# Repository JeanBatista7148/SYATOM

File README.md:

# SYATOM
Aqui encontraras todos los documentos del proyecto SYATOM

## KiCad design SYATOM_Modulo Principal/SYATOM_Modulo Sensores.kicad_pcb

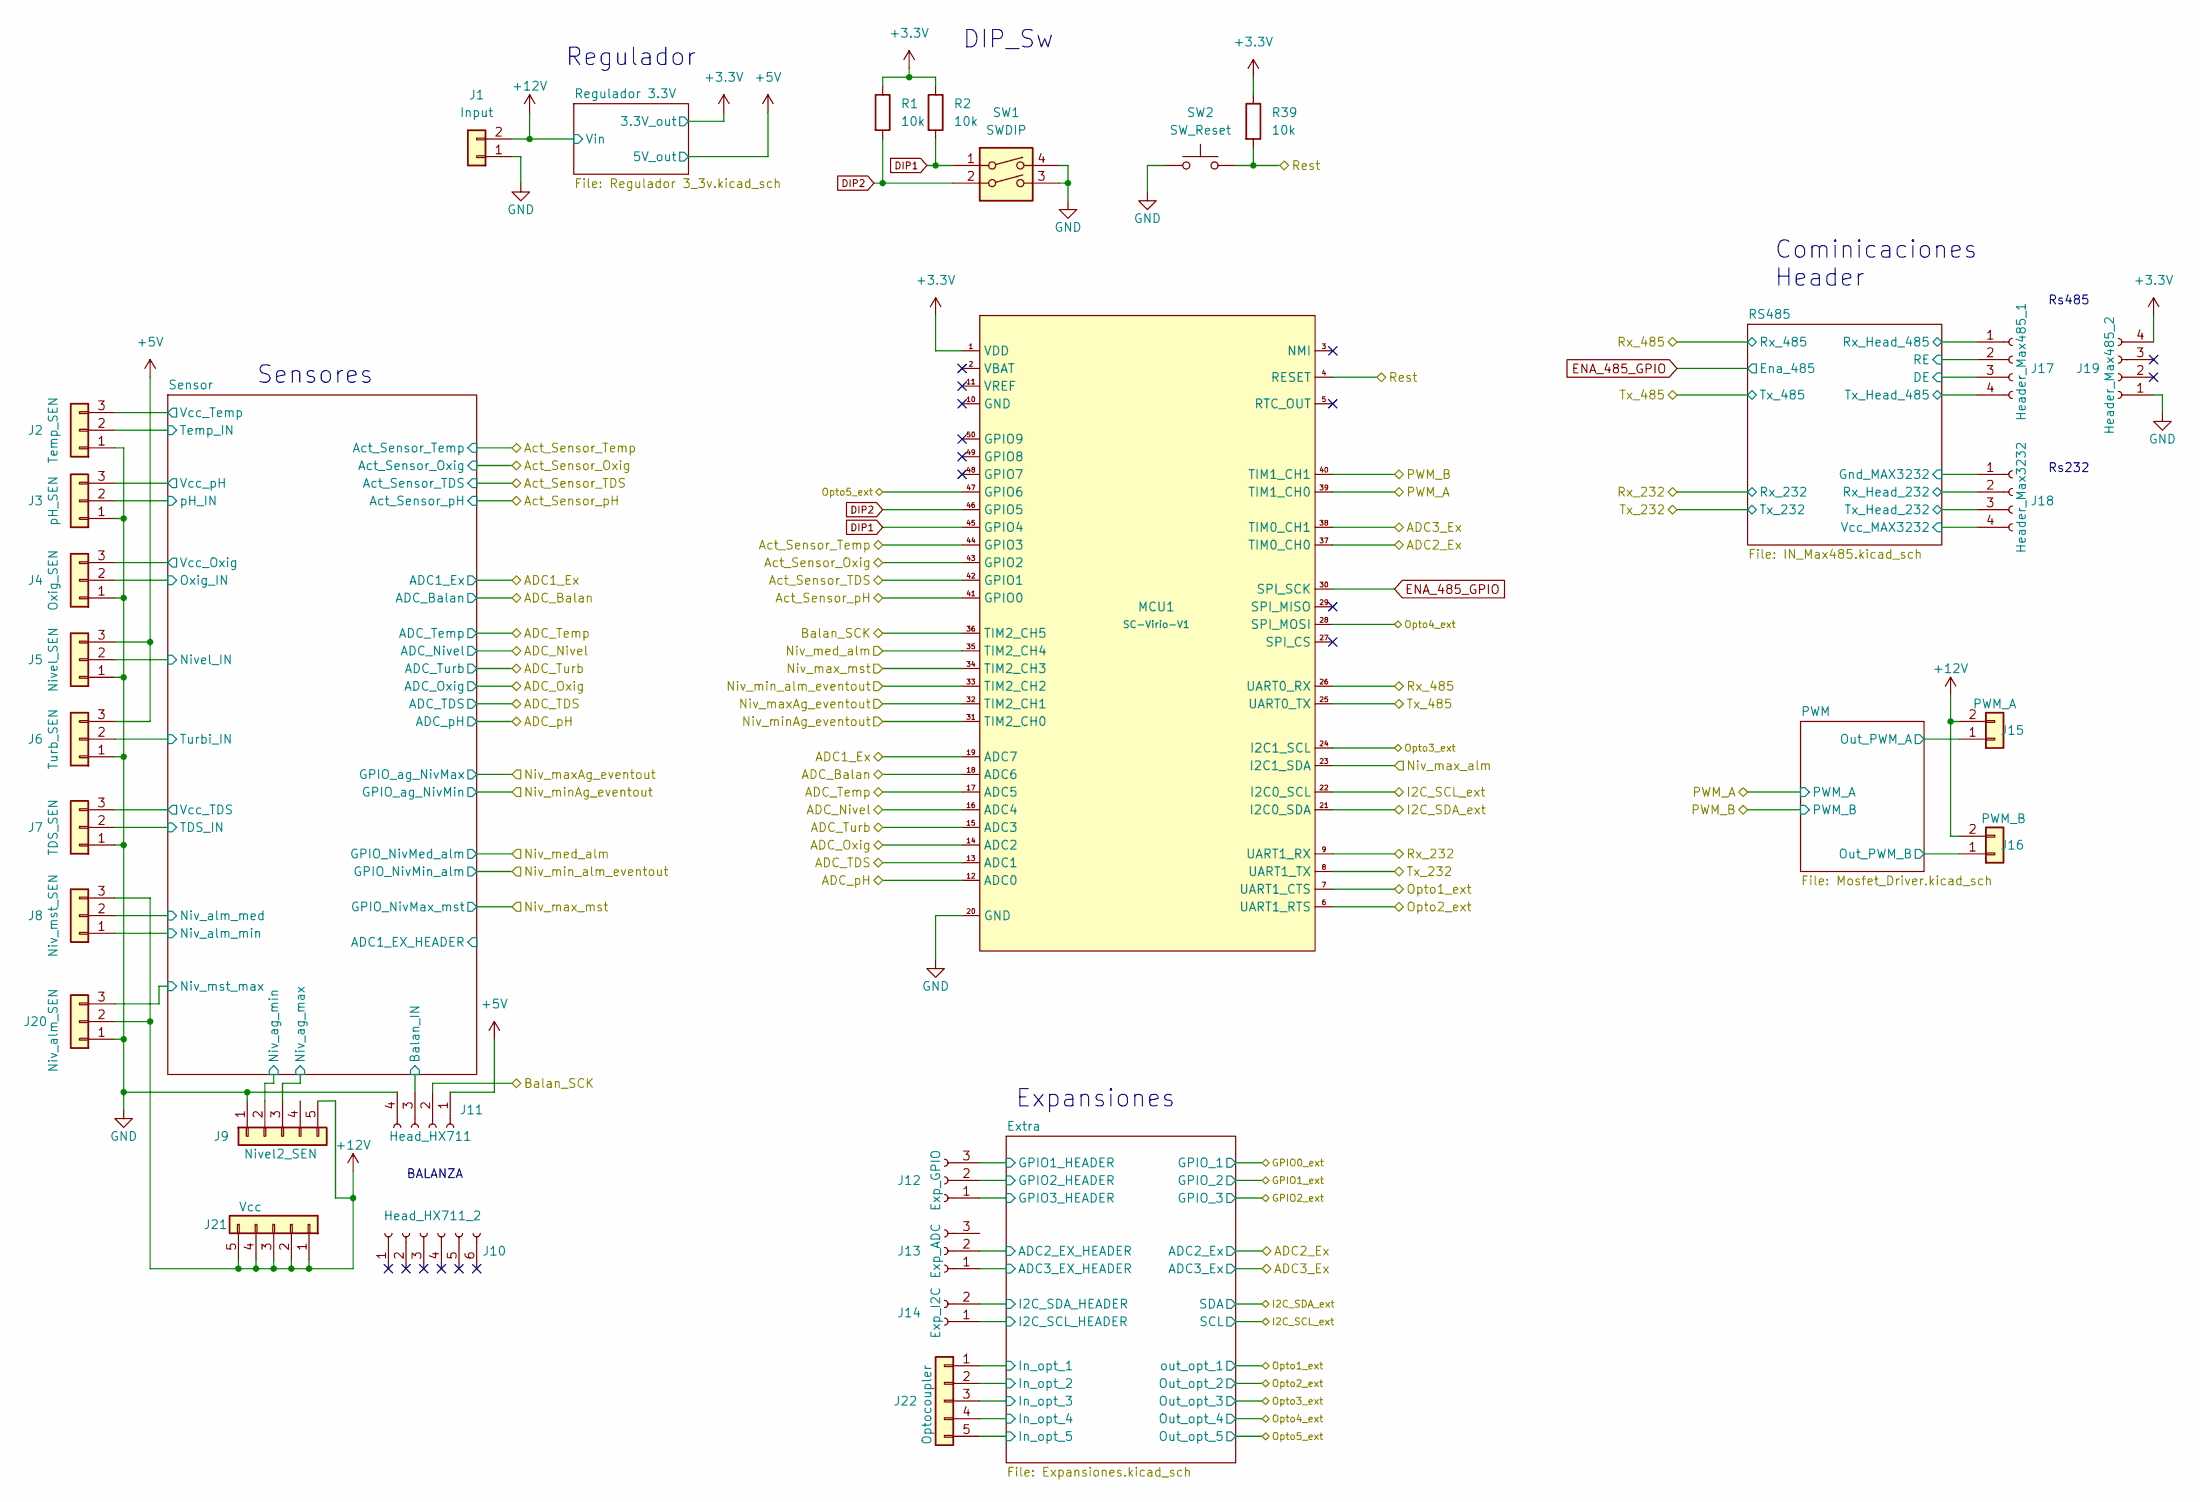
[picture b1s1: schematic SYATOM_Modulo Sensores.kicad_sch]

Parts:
J1: Input; TerminalBlock_bornier-2_P5.08mm
J2: Temp_SEN; TerminalBlock_bornier-3_P5.08mm
J3: pH_SEN; TerminalBlock_bornier-3_P5.08mm
J4: Oxig_SEN; TerminalBlock_bornier-3_P5.08mm
J5: Nivel_SEN; TerminalBlock_bornier-3_P5.08mm
J6: Turb_SEN; TerminalBlock_bornier-3_P5.08mm
J7: TDS_SEN; TerminalBlock_bornier-3_P5.08mm
J8: Niv_mst_SEN; TerminalBlock_bornier-3_P5.08mm
J9: Nivel2_SEN; TerminalBlock_bornier-5_P5.08mm
J10: Head_HX711_2; PinSocket_1x06_P2.54mm_Vertical
J11: Head_HX711; PinSocket_1x04_P2.54mm_Vertical
J12: Exp_GPIO; PinSocket_1x03_P2.54mm_Vertical
J13: Exp_ADC; PinSocket_1x03_P2.54mm_Vertical
J14: Exp_I2C; PinSocket_1x02_P2.54mm_Vertical
J15: PWM_A; TerminalBlock_bornier-2_P5.08mm
J16: PWM_B; TerminalBlock_bornier-2_P5.08mm
J17: Header_Max485_1; PinSocket_1x04_P2.54mm_Vertical
J18: Header_Max3232; PinSocket_1x04_P2.54mm_Vertical
J19: Header_Max485_2; PinSocket_1x04_P2.54mm_Vertical
J20: Niv_alm_SEN; TerminalBlock_bornier-3_P5.08mm
J21: Vcc; TerminalBlock_bornier-5_P5.08mm
J22: Optocoupler; TerminalBlock_bornier-5_P5.08mm
MCU1: SC-Virio-V1; SC-VIRIO-V1
R1, R2, R39: 10k; R_0603_1608Metric
SW1: SWDIP; SW_DIP_SPSTx02_Slide_9.78x7.26mm_W7.62mm_P2.54mm
SW2: SW_Reset; SW_SPST_B3S-1000

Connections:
+3V3: J18.4, J19.4, MCU1.1 (VDD), R1.1, R2.1, R39.1; also elsewhere on the board
+5V: J5.3, J6.3, J11.1; also elsewhere on the board
+12V: J1.2, J8.3, J9.5, J15.2, J16.2, J20.2, J21.1, J21.2, J21.3, J21.4, J21.5; also elsewhere on the board
/ADC1_Ex: MCU1.19 (ADC7); also elsewhere on the board
/ADC2_Ex: MCU1.37 (TIM0_CH0); also elsewhere on the board
/ADC3_Ex: MCU1.38 (TIM0_CH1); also elsewhere on the board
/ADC_Balan: MCU1.18 (ADC6); also elsewhere on the board
/ADC_Nivel: MCU1.16 (ADC4); also elsewhere on the board
/ADC_Oxig: MCU1.14 (ADC2); also elsewhere on the board
/ADC_TDS: MCU1.13 (ADC1); also elsewhere on the board
/ADC_Temp: MCU1.17 (ADC5); also elsewhere on the board
/ADC_Turb: MCU1.15 (ADC3); also elsewhere on the board
/ADC_pH: MCU1.12 (ADC0); also elsewhere on the board
/Act_Sensor_Oxig: MCU1.43 (GPIO2); also elsewhere on the board
/Act_Sensor_TDS: MCU1.42 (GPIO1); also elsewhere on the board
/Act_Sensor_Temp: MCU1.44 (GPIO3); also elsewhere on the board
/Act_Sensor_pH: MCU1.41 (GPIO0); also elsewhere on the board
/Balan_SCK: J11.2, MCU1.36 (TIM2_CH5)
/Extra/ADC2_EX_HEADER: J13.2; also elsewhere on the board
/Extra/ADC3_EX_HEADER: J13.1; also elsewhere on the board
/Extra/In_opt_1: J22.1; also elsewhere on the board
/Extra/In_opt_2: J22.2; also elsewhere on the board
/Extra/In_opt_3: J22.3; also elsewhere on the board
/Extra/In_opt_4: J22.4; also elsewhere on the board
/Extra/In_opt_5: J22.5; also elsewhere on the board
/GPIO0_ext: J12.3; also elsewhere on the board
/GPIO1_ext: J12.2; also elsewhere on the board
/GPIO2_ext: J12.1; also elsewhere on the board
/I2C_SCL_ext: J14.1, MCU1.22 (I2C0_SCL); also elsewhere on the board
/I2C_SDA_ext: J14.2, MCU1.21 (I2C0_SDA); also elsewhere on the board
/Niv_maxAg_eventout: MCU1.32 (TIM2_CH1); also elsewhere on the board
/Niv_max_alm: MCU1.23 (I2C1_SDA)
/Niv_max_mst: MCU1.34 (TIM2_CH3); also elsewhere on the board
/Niv_med_alm: MCU1.35 (TIM2_CH4); also elsewhere on the board
/Niv_minAg_eventout: MCU1.31 (TIM2_CH0); also elsewhere on the board
/Niv_min_alm_eventout: MCU1.33 (TIM2_CH2); also elsewhere on the board
/Opto1_ext: MCU1.7 (UART1_CTS); also elsewhere on the board
/Opto2_ext: MCU1.6 (UART1_RTS); also elsewhere on the board
/Opto3_ext: MCU1.24 (I2C1_SCL); also elsewhere on the board
/Opto4_ext: MCU1.28 (SPI_MOSI); also elsewhere on the board
/Opto5_ext: MCU1.47 (GPIO6); also elsewhere on the board
/PWM/Out_PWM_A: J15.1; also elsewhere on the board
/PWM/Out_PWM_B: J16.1; also elsewhere on the board
/PWM_A: MCU1.39 (TIM1_CH0); also elsewhere on the board
/PWM_B: MCU1.40 (TIM1_CH1); also elsewhere on the board
/Rest: MCU1.4 (RESET), R39.2, SW2.2
/Rx_232: J18.2, MCU1.9 (UART1_RX); also elsewhere on the board
/Rx_485: J17.1, MCU1.26 (UART0_RX); also elsewhere on the board
/Sensor /Balan_IN: J11.3; also elsewhere on the board
/Sensor /Niv_ag_max: J9.3; also elsewhere on the board
/Sensor /Niv_ag_min: J9.2; also elsewhere on the board
/Sensor /Niv_alm_med: J8.2; also elsewhere on the board
/Sensor /Niv_alm_min: J8.1; also elsewhere on the board
/Sensor /Niv_mst_max: J20.3; also elsewhere on the board
/Sensor /Nivel_IN: J5.2; also elsewhere on the board
/Sensor /Oxig_IN: J4.2; also elsewhere on the board
/Sensor /TDS_IN: J7.2; also elsewhere on the board
/Sensor /Temp_IN: J2.2; also elsewhere on the board
/Sensor /Turbi_IN: J6.2; also elsewhere on the board
/Sensor /Vcc_Oxig: J4.3; also elsewhere on the board
/Sensor /Vcc_TDS: J7.3; also elsewhere on the board
/Sensor /Vcc_Temp: J2.3; also elsewhere on the board
/Sensor /Vcc_pH: J3.3; also elsewhere on the board
/Sensor /pH_IN: J3.2; also elsewhere on the board
/Tx_232: J18.3, MCU1.8 (UART1_TX); also elsewhere on the board
/Tx_485: J17.4, MCU1.25 (UART0_TX); also elsewhere on the board
DIP1: MCU1.45 (GPIO4), R2.2, SW1.1
DIP2: MCU1.46 (GPIO5), R1.2, SW1.2
ENA_485_GPIO: J17.2, J17.3, MCU1.30 (SPI_SCK); also elsewhere on the board
GND: J1.1, J2.1, J3.1, J4.1, J5.1, J6.1, J7.1, J9.1, J11.4, J18.1, J19.1, J20.1, MCU1.20 (GND), SW1.3, SW1.4, SW2.1; also elsewhere on the board

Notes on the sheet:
Cominicaciones Header
Rs485
Regulador
Rs232
Sensores
DIP_Sw
Expansiones
BALANZA

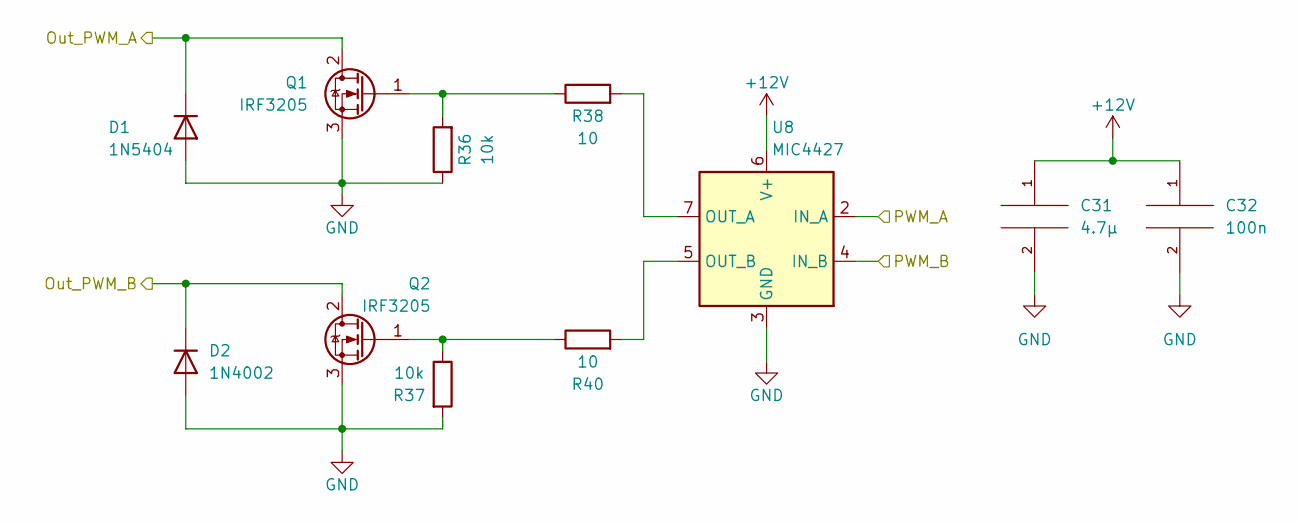
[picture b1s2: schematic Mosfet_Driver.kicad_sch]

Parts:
C31: 4.7µ; C_0805_2012Metric
C32: 100n; C_0603_1608Metric
D1: 1N5404; D_DO-201AD_P15.24mm_Horizontal
D2: 1N4002; D_DO-41_SOD81_P10.16mm_Horizontal
Q1, Q2: IRF3205; TO-220-3_Vertical
R36, R37: 10k; R_0603_1608Metric
R38, R40: 10; R_0603_1608Metric
U8: MIC4427; SOIC-8_3.9x4.9mm_P1.27mm

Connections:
+12V: C31.1, C32.1, U8.6 (V+); also elsewhere on the board
/PWM/Out_PWM_A: D1.1 (K), Q1.2 (D); also elsewhere on the board
/PWM/Out_PWM_B: D2.1 (K), Q2.2 (D); also elsewhere on the board
/PWM_A: U8.2 (IN_A); also elsewhere on the board
/PWM_B: U8.4 (IN_B); also elsewhere on the board
GND: C31.2, C32.2, D1.2 (A), D2.2 (A), Q1.3 (S), Q2.3 (S), R36.1, R37.2, U8.3 (GND); also elsewhere on the board
unnamed: Q1.1 (G), R36.2, R38.1
unnamed: Q2.1 (G), R37.1, R40.1
unnamed: R38.2, U8.7 (OUT_A)
unnamed: R40.2, U8.5 (OUT_B)

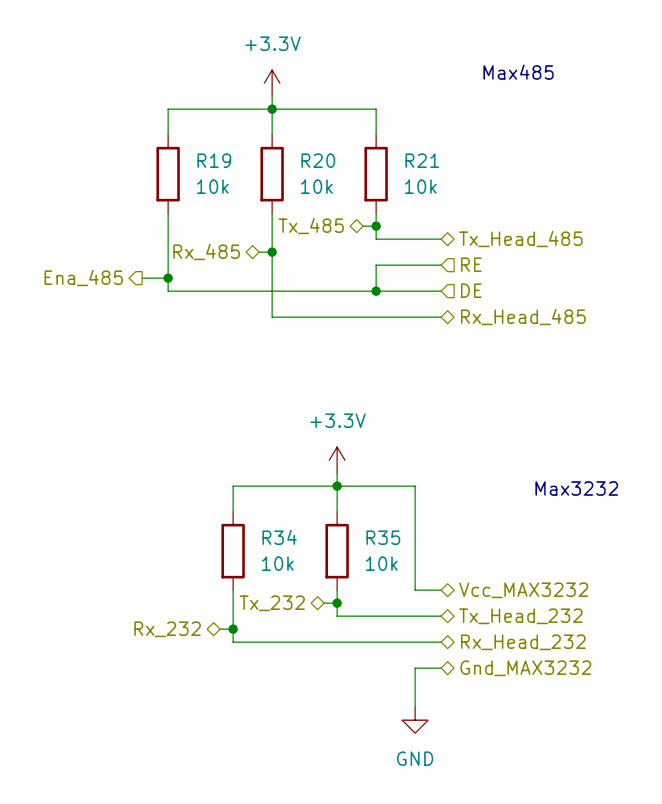
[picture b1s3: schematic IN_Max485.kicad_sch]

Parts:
R19, R20, R21, R34, R35: 10k; R_0603_1608Metric

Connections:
+3V3: R19.1, R20.1, R21.1, R34.1, R35.1; also elsewhere on the board
/Rx_232: R34.2; also elsewhere on the board
/Rx_485: R20.2; also elsewhere on the board
/Tx_232: R35.2; also elsewhere on the board
/Tx_485: R21.2; also elsewhere on the board
ENA_485_GPIO: R19.2; also elsewhere on the board

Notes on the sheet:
Max3232
Max485

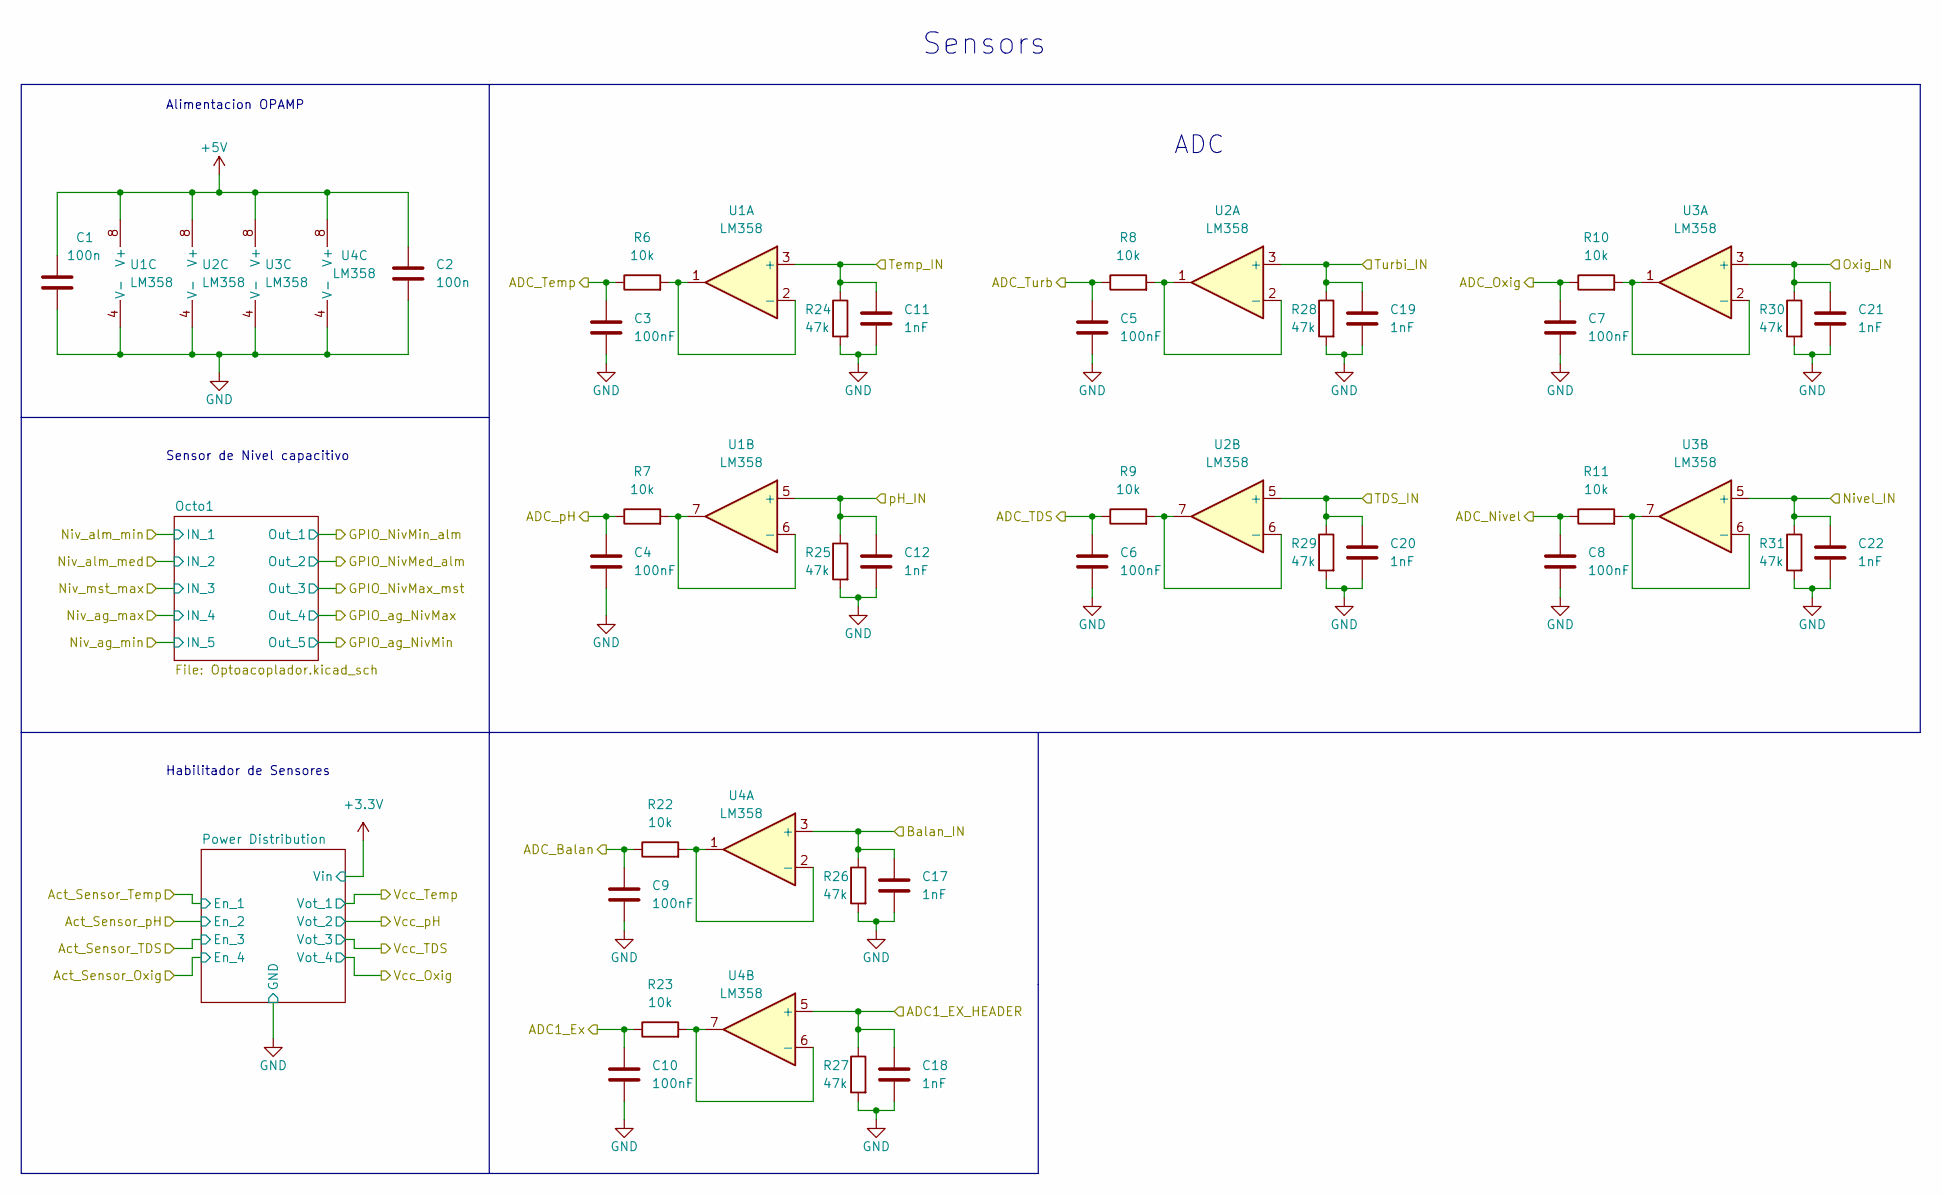
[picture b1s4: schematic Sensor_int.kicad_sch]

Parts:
C1, C2: 100n; C_0603_1608Metric
C3, C4, C5, C6, C7, C8, C9, C10: 100nF; C_0603_1608Metric
C11, C12, C17, C18, C19, C20, C21, C22: 1nF; C_0603_1608Metric
R6, R7, R8, R9, R10, R11, R22, R23: 10k; R_0603_1608Metric
R24, R25, R26, R27, R28, R29, R30, R31: 47k; R_0603_1608Metric
U1, U2, U3, U4: LM358; SOIC-8_3.9x4.9mm_P1.27mm

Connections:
+5V: C1.1, C2.1, U1.8 (V+), U2.8 (V+), U3.8 (V+), U4.8 (V+); also elsewhere on the board
/ADC1_Ex: C10.1, R23.1; also elsewhere on the board
/ADC_Balan: C9.1, R22.1; also elsewhere on the board
/ADC_Nivel: C8.1, R11.1; also elsewhere on the board
/ADC_Oxig: C7.1, R10.1; also elsewhere on the board
/ADC_TDS: C6.1, R9.1; also elsewhere on the board
/ADC_Temp: C3.1, R6.1; also elsewhere on the board
/ADC_Turb: C5.1, R8.1; also elsewhere on the board
/ADC_pH: C4.1, R7.1; also elsewhere on the board
/Sensor /ADC1_EX_HEADER: C18.1, R27.1, U4.5 (+)
/Sensor /Balan_IN: C17.1, R26.1, U4.3 (+); also elsewhere on the board
/Sensor /Nivel_IN: C22.1, R31.1, U3.5 (+); also elsewhere on the board
/Sensor /Oxig_IN: C21.1, R30.1, U3.3 (+); also elsewhere on the board
/Sensor /TDS_IN: C20.1, R29.1, U2.5 (+); also elsewhere on the board
/Sensor /Temp_IN: C11.1, R24.1, U1.3 (+); also elsewhere on the board
/Sensor /Turbi_IN: C19.1, R28.1, U2.3 (+); also elsewhere on the board
/Sensor /pH_IN: C12.1, R25.1, U1.5 (+); also elsewhere on the board
GND: C1.2, C2.2, C3.2, C4.2, C5.2, C6.2, C7.2, C8.2, C9.2, C10.2, C11.2, C12.2, C17.2, C18.2, C19.2, C20.2, C21.2, C22.2, R24.2, R25.2, R26.2, R27.2, R28.2, R29.2, R30.2, R31.2, U1.4 (V-), U2.4 (V-), U3.4 (V-), U4.4 (V-); also elsewhere on the board
unnamed: R6.2, U1.1, U1.2 (-)
unnamed: R7.2, U1.6 (-), U1.7
unnamed: R8.2, U2.1, U2.2 (-)
unnamed: R9.2, U2.6 (-), U2.7
unnamed: R10.2, U3.1, U3.2 (-)
unnamed: R11.2, U3.6 (-), U3.7
unnamed: R22.2, U4.1, U4.2 (-)
unnamed: R23.2, U4.6 (-), U4.7

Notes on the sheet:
ADC
Sensor de Nivel capacitivo
Sensors
Habilitador de Sensores
Alimentacion OPAMP

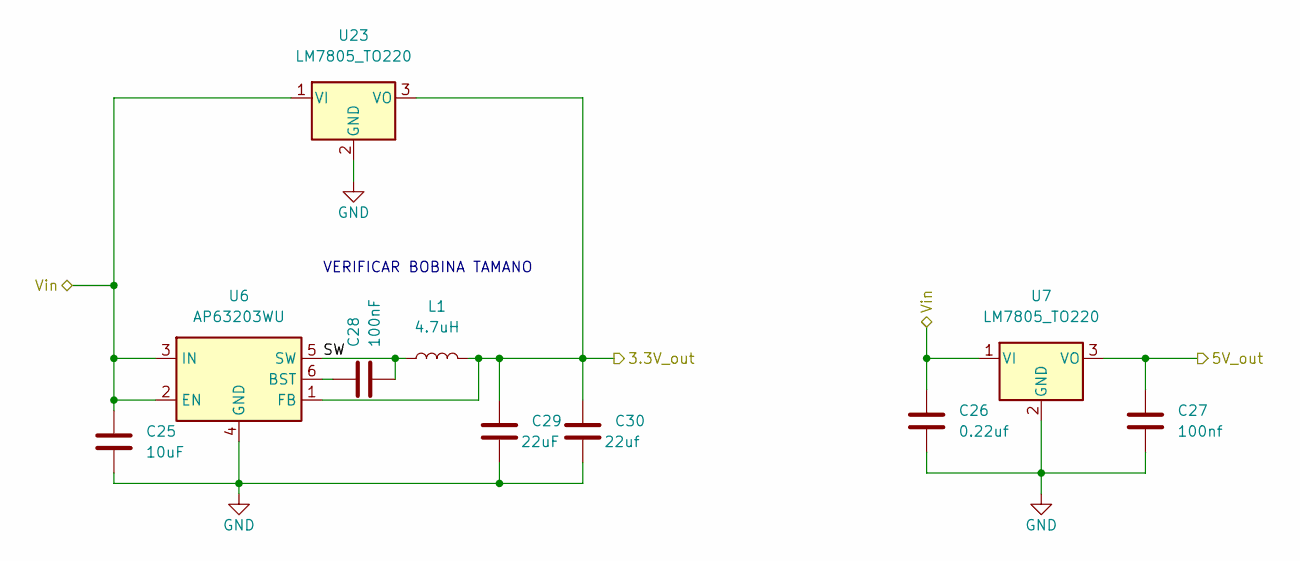
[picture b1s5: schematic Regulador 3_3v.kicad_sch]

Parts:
C25: 10uF; C_0805_2012Metric
C26: 0.22uf; C_0805_2012Metric
C27: 100nf; C_0603_1608Metric
C28: 100nF; C_0603_1608Metric
C29: 22uF; C_0805_2012Metric
C30: 22uf; C_0805_2012Metric
L1: 4.7uH; L_Bourns_SRN6045TA
U6: AP63203WU; TSOT-23-6
U7, U23: LM7805_TO220; TO-220-3_Vertical

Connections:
+3V3: C29.1, C30.1, L1.2, U6.1 (FB), U23.3 (VO); also elsewhere on the board
+5V: C27.1, U7.3 (VO); also elsewhere on the board
+12V: C25.1, C26.1, U6.2 (EN), U6.3 (IN), U7.1 (VI), U23.1 (VI); also elsewhere on the board
GND: C25.2, C26.2, C27.2, C29.2, C30.2, U6.4 (GND), U7.2 (GND), U23.2 (GND); also elsewhere on the board
unnamed: C28.1, L1.1, U6.5 (SW)
unnamed: C28.2, U6.6 (BST)

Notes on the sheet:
VERIFICAR BOBINA TAMANO

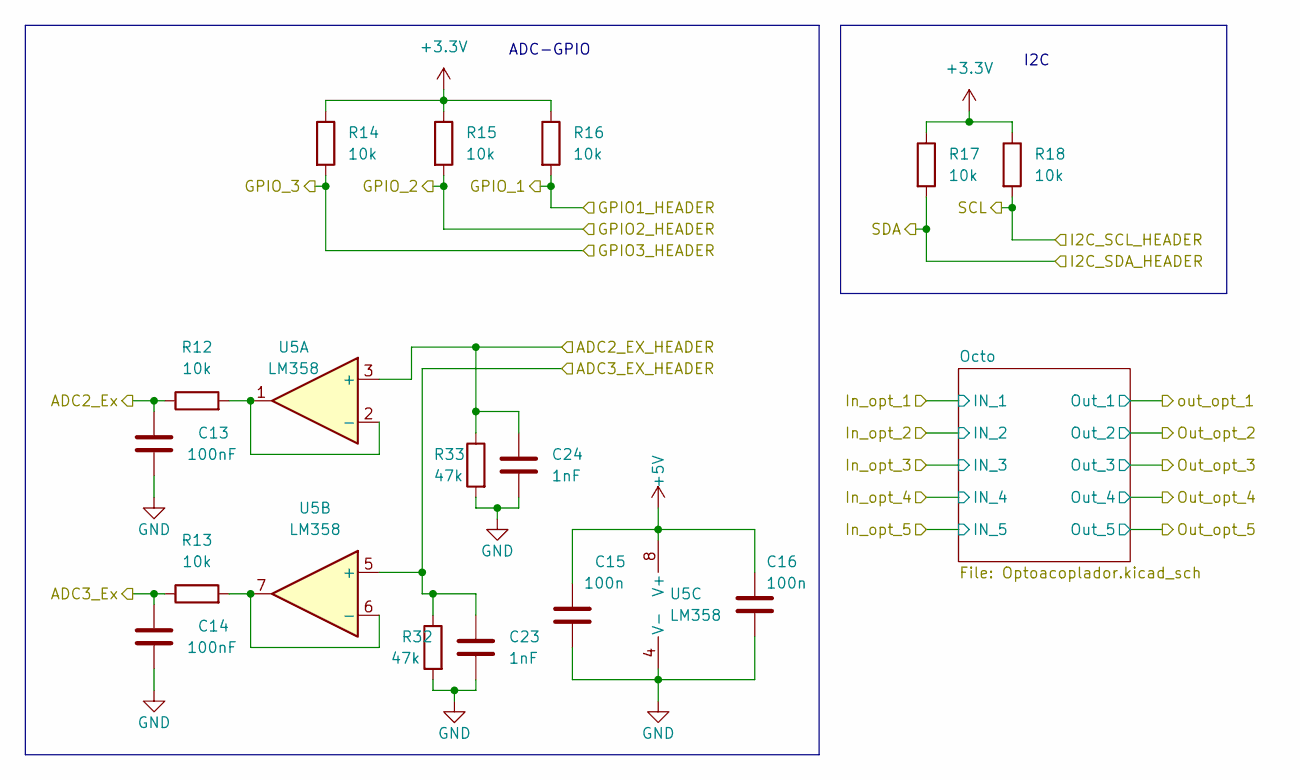
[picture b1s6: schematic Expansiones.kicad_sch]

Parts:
C13, C14: 100nF; C_0603_1608Metric
C15, C16: 100n; C_0603_1608Metric
C23, C24: 1nF; C_0603_1608Metric
R12, R13, R14, R15, R16, R17, R18: 10k; R_0603_1608Metric
R32, R33: 47k; R_0603_1608Metric
U5: LM358; SOIC-8_3.9x4.9mm_P1.27mm

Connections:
+3V3: R14.1, R15.1, R16.1, R17.1, R18.1; also elsewhere on the board
+5V: C15.1, C16.1, U5.8 (V+); also elsewhere on the board
/ADC2_Ex: C13.1, R12.1; also elsewhere on the board
/ADC3_Ex: C14.1, R13.1; also elsewhere on the board
/Extra/ADC2_EX_HEADER: C24.1, R33.1, U5.3 (+); also elsewhere on the board
/Extra/ADC3_EX_HEADER: C23.1, R32.1, U5.5 (+); also elsewhere on the board
/GPIO0_ext: R16.2; also elsewhere on the board
/GPIO1_ext: R15.2; also elsewhere on the board
/GPIO2_ext: R14.2; also elsewhere on the board
/I2C_SCL_ext: R18.2; also elsewhere on the board
/I2C_SDA_ext: R17.2; also elsewhere on the board
GND: C13.2, C14.2, C15.2, C16.2, C23.2, C24.2, R32.2, R33.2, U5.4 (V-); also elsewhere on the board
unnamed: R12.2, U5.1, U5.2 (-)
unnamed: R13.2, U5.6 (-), U5.7

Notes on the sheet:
ADC-GPIO
I2C

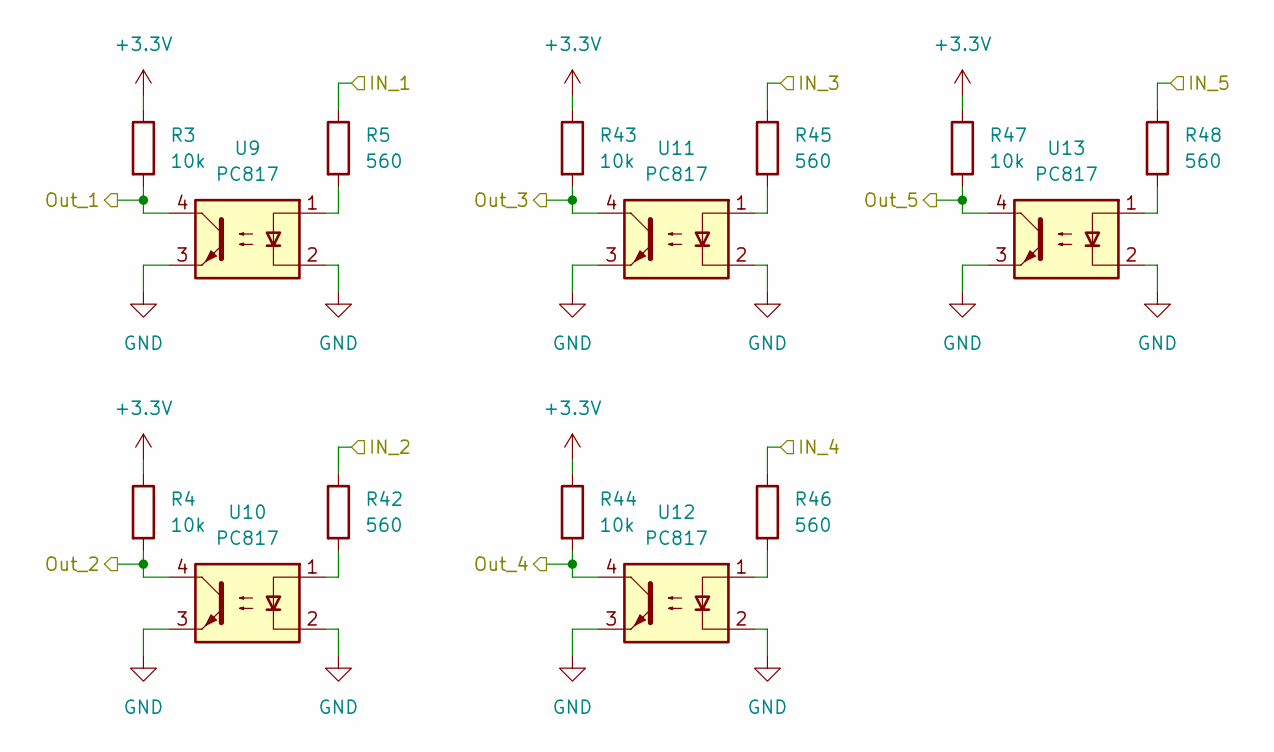
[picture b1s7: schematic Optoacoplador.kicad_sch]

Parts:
R3, R4, R43, R44, R47: 10k; R_0603_1608Metric
R5, R42, R45, R46, R48: 560; R_0603_1608Metric
U9, U10, U11, U12, U13: PC817; DIP-4_W7.62mm_SMDSocket_SmallPads

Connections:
+3V3: R3.1, R4.1, R43.1, R44.1, R47.1; also elsewhere on the board
/Niv_maxAg_eventout: R44.2, U12.4; also elsewhere on the board
/Niv_max_mst: R43.2, U11.4; also elsewhere on the board
/Niv_med_alm: R4.2, U10.4; also elsewhere on the board
/Niv_minAg_eventout: R47.2, U13.4; also elsewhere on the board
/Niv_min_alm_eventout: R3.2, U9.4; also elsewhere on the board
/Sensor /Niv_ag_max: R46.1; also elsewhere on the board
/Sensor /Niv_ag_min: R48.1; also elsewhere on the board
/Sensor /Niv_alm_med: R42.1; also elsewhere on the board
/Sensor /Niv_alm_min: R5.1; also elsewhere on the board
/Sensor /Niv_mst_max: R45.1; also elsewhere on the board
GND: U9.2, U9.3, U10.2, U10.3, U11.2, U11.3, U12.2, U12.3, U13.2, U13.3; also elsewhere on the board
unnamed: R5.2, U9.1
unnamed: R42.2, U10.1
unnamed: R45.2, U11.1
unnamed: R46.2, U12.1
unnamed: R48.2, U13.1

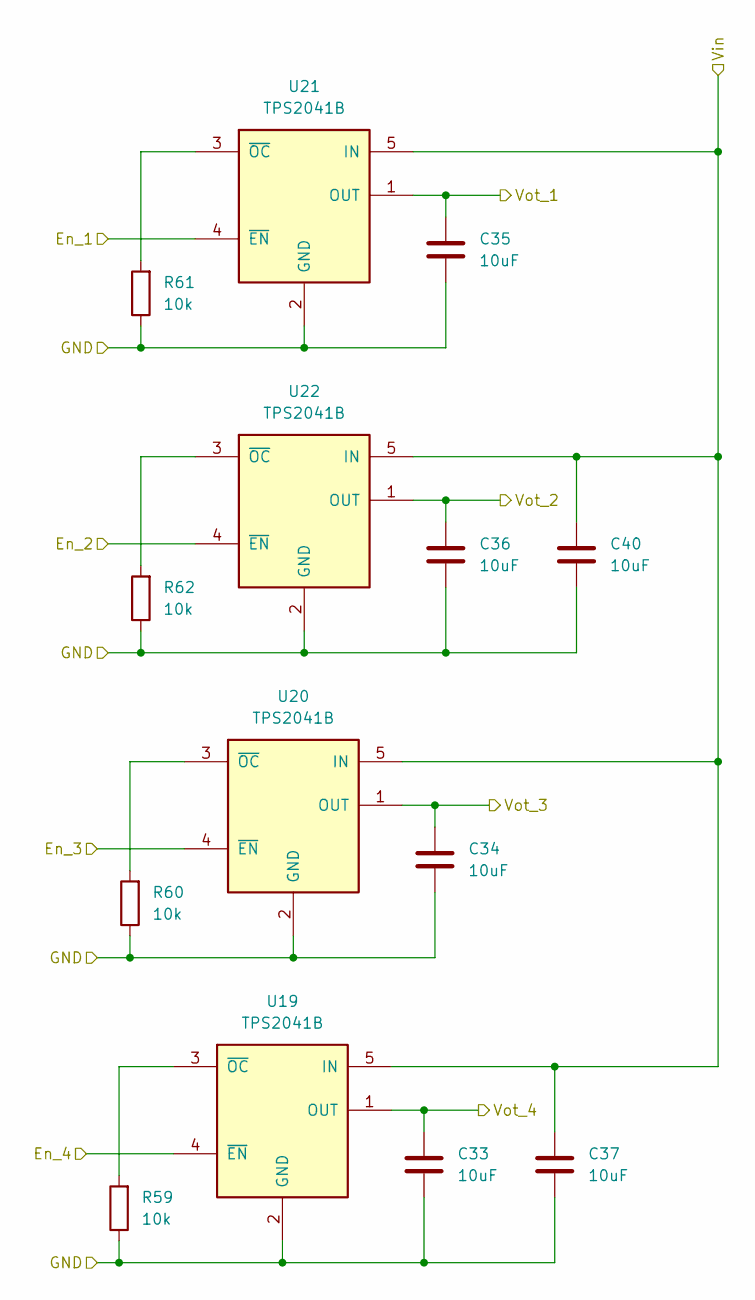
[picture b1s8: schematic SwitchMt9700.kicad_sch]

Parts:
C33, C34, C35, C36, C37, C40: 10uF; C_0805_2012Metric
R59, R60, R61, R62: 10k; R_0603_1608Metric
U19, U20, U21, U22: TPS2041B; SOT-23-5

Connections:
+3V3: C37.1, C40.1, U19.5 (IN), U20.5 (IN), U21.5 (IN), U22.5 (IN); also elsewhere on the board
/Act_Sensor_Oxig: U19.4 (~EN); also elsewhere on the board
/Act_Sensor_TDS: U20.4 (~EN); also elsewhere on the board
/Act_Sensor_Temp: U21.4 (~EN); also elsewhere on the board
/Act_Sensor_pH: U22.4 (~EN); also elsewhere on the board
/Sensor /Vcc_Oxig: C33.1, U19.1 (OUT); also elsewhere on the board
/Sensor /Vcc_TDS: C34.1, U20.1 (OUT); also elsewhere on the board
/Sensor /Vcc_Temp: C35.1, U21.1 (OUT); also elsewhere on the board
/Sensor /Vcc_pH: C36.1, U22.1 (OUT); also elsewhere on the board
GND: C33.2, C34.2, C35.2, C36.2, C37.2, C40.2, R59.1, R60.1, R61.1, R62.1, U19.2 (GND), U20.2 (GND), U21.2 (GND), U22.2 (GND); also elsewhere on the board
unnamed: R59.2, U19.3 (~OC)
unnamed: R60.2, U20.3 (~OC)
unnamed: R61.2, U21.3 (~OC)
unnamed: R62.2, U22.3 (~OC)

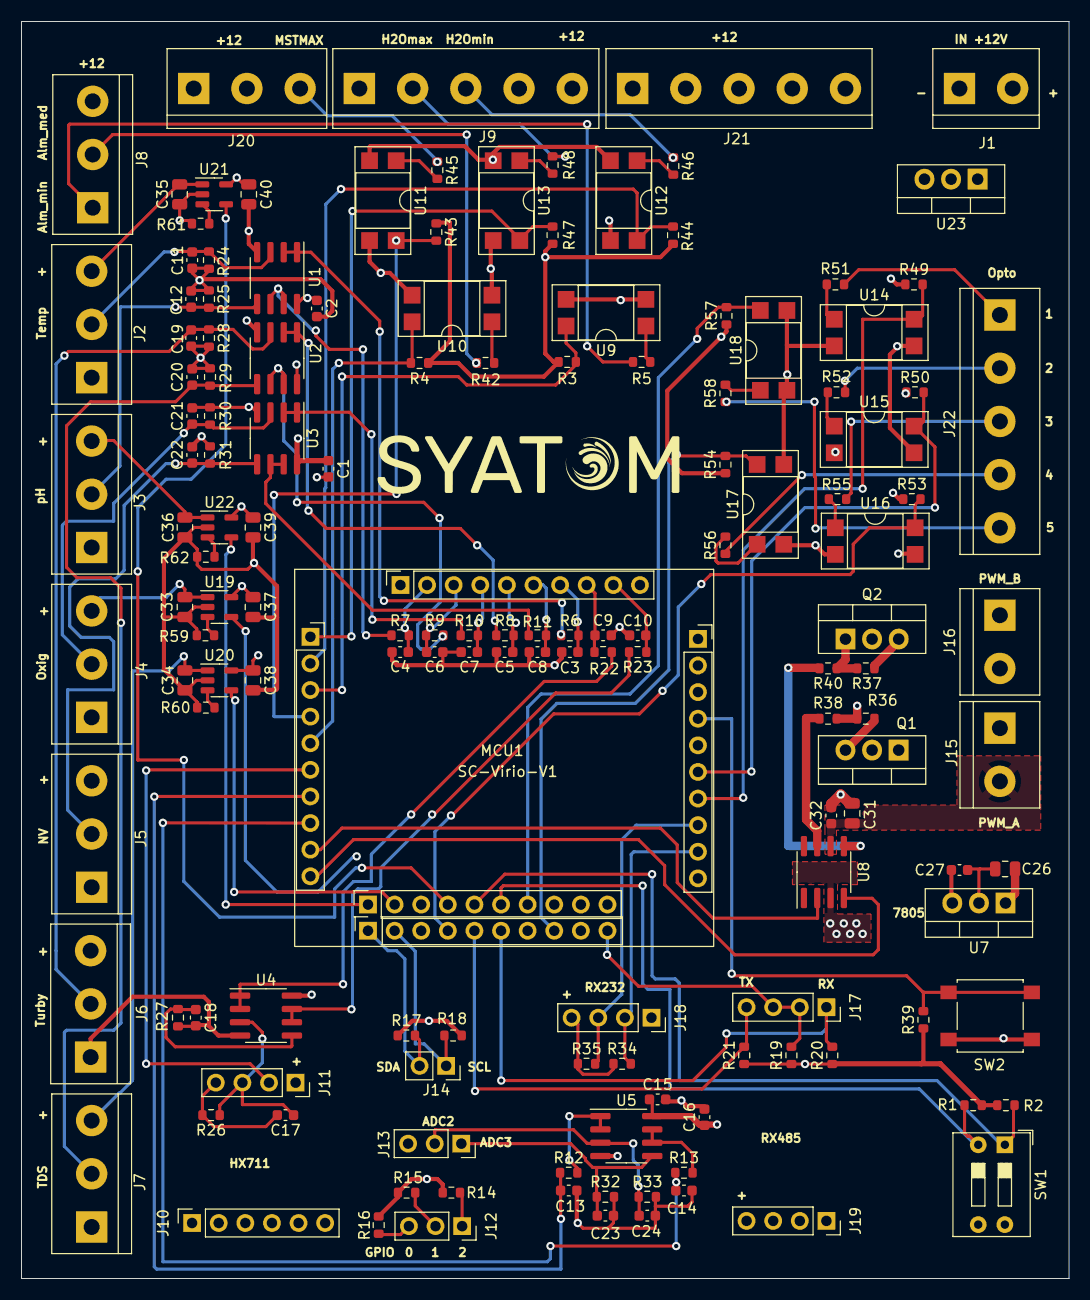
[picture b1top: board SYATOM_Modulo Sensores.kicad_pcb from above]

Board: 4 copper layers, 100.0 x 120.0 mm, 148 parts (1 on the bottom side), 98 nets.

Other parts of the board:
C38, C39: 10uF; C_0805_2012Metric
GE: LOGO; Isologo_SYATOM
GE#2: LOGO; Isologo_SYATOM
R49, R50, R53, R54, R57: 10k; R_0603_1608Metric
R51, R52, R55, R56, R58: 560; R_0603_1608Metric
U14, U15, U16, U17, U18: PC817; DIP-4_W7.62mm_SMDSocket_SmallPads

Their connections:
+3V3: C38.1, C39.1, R49.1, R50.1, R53.1, R54.1, R57.1; also elsewhere on the board
/Extra/In_opt_1: R51.1; also elsewhere on the board
/Extra/In_opt_2: R52.1; also elsewhere on the board
/Extra/In_opt_3: R55.1; also elsewhere on the board
/Extra/In_opt_4: R56.1; also elsewhere on the board
/Extra/In_opt_5: R58.1; also elsewhere on the board
/Opto1_ext: R49.2, U14.4; also elsewhere on the board
/Opto2_ext: R50.2, U15.4; also elsewhere on the board
/Opto3_ext: R53.2, U16.4; also elsewhere on the board
/Opto4_ext: R54.2, U17.4; also elsewhere on the board
/Opto5_ext: R57.2, U18.4; also elsewhere on the board
GND: C38.2, C39.2, U14.2, U14.3, U15.2, U15.3, U16.2, U16.3, U17.2, U17.3, U18.2, U18.3; also elsewhere on the board
unnamed: R51.2, U14.1
unnamed: R52.2, U15.1
unnamed: R55.2, U16.1
unnamed: R56.2, U17.1
unnamed: R58.2, U18.1

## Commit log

2022-10-29 Add files via upload
    PCB principal Versión I
2022-10-29 Add files via upload
    Se agrego el silkscreen de los logos y label de los conectores, ademas una resistencia pull-up al botón reset
